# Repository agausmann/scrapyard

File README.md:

# scrapyard

Turning salvaged electronics into MIDI instruments

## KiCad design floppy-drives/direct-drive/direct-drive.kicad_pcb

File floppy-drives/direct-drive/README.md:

# Direct Drive

A floppy drive driver that attaches directly to the drive's IDC connector.

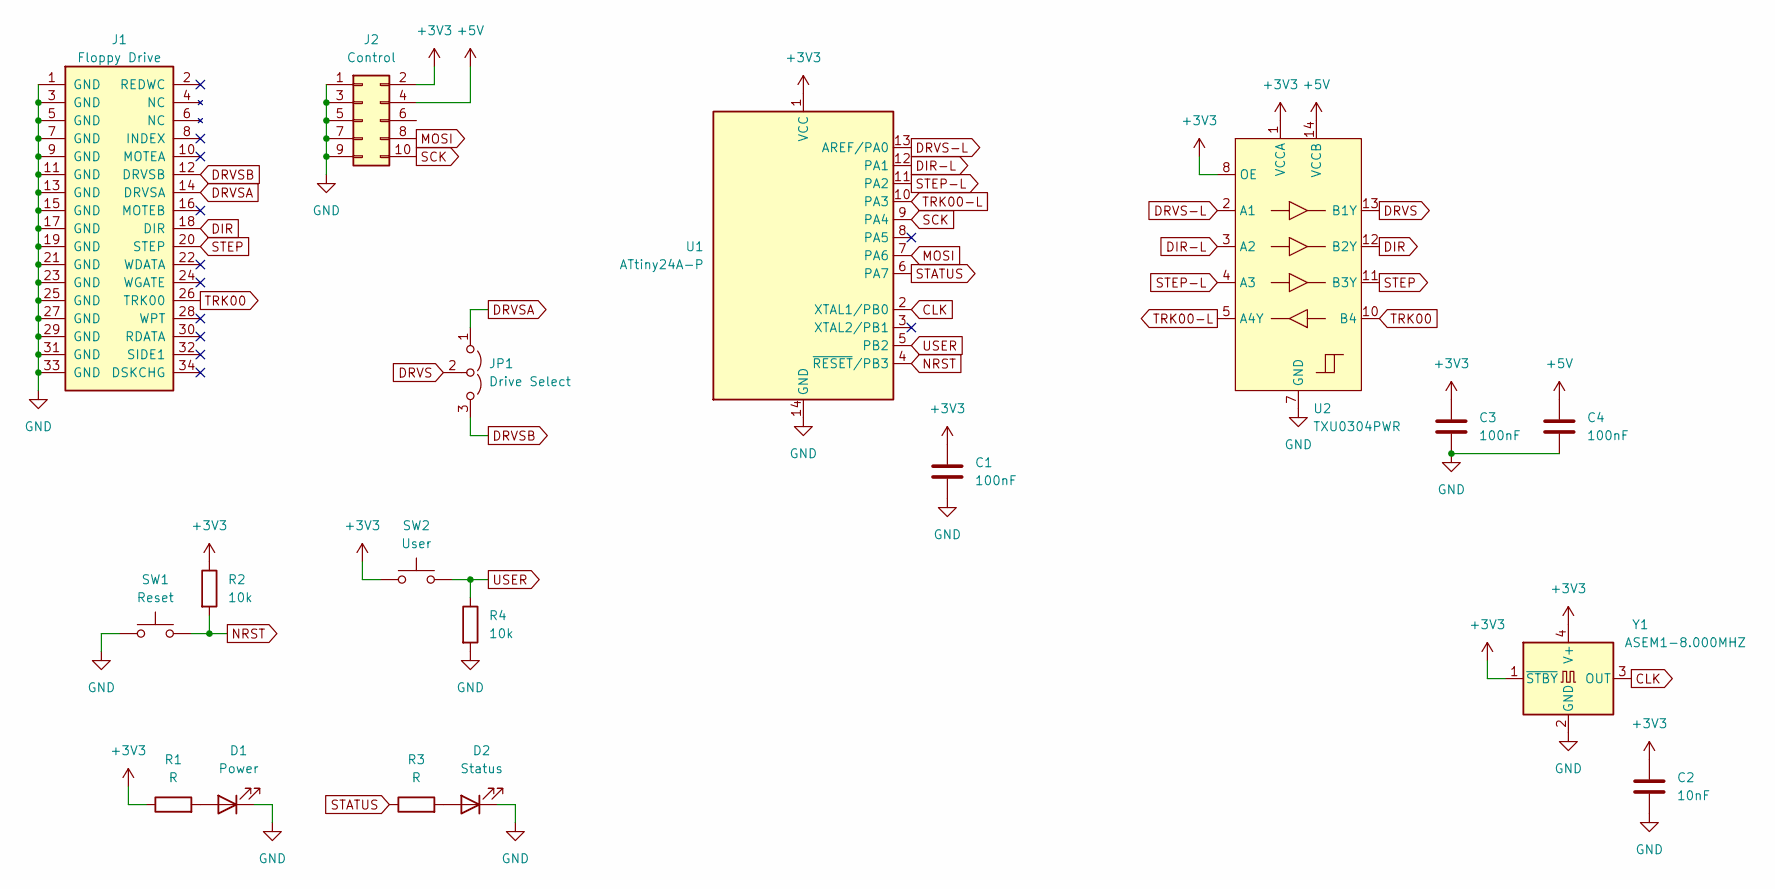
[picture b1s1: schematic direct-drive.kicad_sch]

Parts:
C1, C3, C4: 100nF; C_0603_1608Metric; Digikey 1276-1005-1-ND
C2: 10nF; C_0603_1608Metric; Digikey 1276-1926-1-ND
D1: Power; LED_0603_1608Metric; Digikey 732-4978-1-ND
D2: Status; LED_0603_1608Metric; Digikey 732-4971-1-ND
J1: Floppy Drive; IDC-Header_2x17_P2.54mm_Horizontal; Digikey S9207-ND
J2: Control; IDC-Header_2x05_P2.54mm_Horizontal; Digikey ED10533-ND
JP1: Drive Select; PinHeader_1x03_P2.54mm_Vertical
R1, R3: R; R_0603_1608Metric
R2, R4: 10k; R_0603_1608Metric
SW1: Reset; SW_Push_1P1T_NO_6x6mm_H9.5mm; Digikey CKN10880CT-ND
SW2: User; SW_Push_1P1T_NO_6x6mm_H9.5mm; Digikey CKN10880CT-ND
U1: ATtiny24A-P; DIP-14_W7.62mm; Digikey ED3045-5-ND
U2: TXU0304PWR; TSSOP-14_4.4x5mm_P0.65mm; Digikey 296-TXU0304PWRCT-ND
Y1: ASEM1-8.000MHZ; ASEM-4Pin-3.2x2.5mm; Digikey 535-9754-1-ND

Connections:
+3V3: C1.1, C2.1, C3.1, J2.2, R1.1, R2.1, SW2.1, U1.1 (VCC), U2.1 (VCCA), U2.8 (OE), Y1.1 (~STBY), Y1.4 (V+)
+5V: C4.1, J2.4, U2.14 (VCCB)
CLK: U1.2 (XTAL1/PB0), Y1.3 (OUT)
DIR: J1.18 (DIR), U2.12 (B2Y)
DIR-L: U1.12 (PA1), U2.3 (A2)
DRVS: JP1.2 (C), U2.13 (B1Y)
DRVS-L: U1.13 (AREF/PA0), U2.2 (A1)
DRVSA: J1.14 (DRVSA), JP1.1 (A)
DRVSB: J1.12 (DRVSB), JP1.3 (B)
GND: C1.2, C2.2, C3.2, C4.2, D1.1 (K), D2.1 (K), J1.1 (GND), J1.3 (GND), J1.5 (GND), J1.7 (GND), J1.9 (GND), J1.11 (GND), J1.13 (GND), J1.15 (GND), J1.17 (GND), J1.19 (GND), J1.21 (GND), J1.23 (GND), J1.25 (GND), J1.27 (GND), J1.29 (GND), J1.31 (GND), J1.33 (GND), J2.1, J2.3, J2.5, J2.7, J2.9, R4.2, SW1.1, U1.14 (GND), U2.7 (GND), Y1.2 (GND)
MOSI: J2.8, U1.7 (PA6)
NRST: R2.2, SW1.2, U1.4 (~RESET/PB3)
unnamed: D1.2 (A), R1.2
unnamed: D2.2 (A), R3.2
SCK: J2.10, U1.9 (PA4)
STATUS: R3.1, U1.6 (PA7)
STEP: J1.20 (STEP), U2.11 (B3Y)
STEP-L: U1.11 (PA2), U2.4 (A3)
TRK00: J1.26 (TRK00), U2.10 (B4)
TRK00-L: U1.10 (PA3), U2.5 (A4Y)
USER: R4.1, SW2.2, U1.5 (PB2)

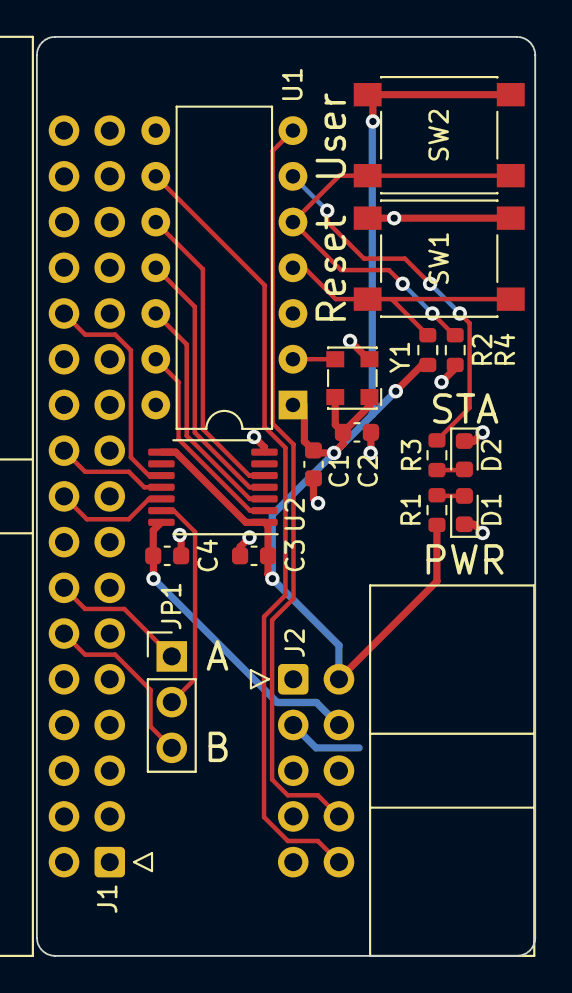
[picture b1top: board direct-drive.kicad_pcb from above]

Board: 2 copper layers, 27.7 x 51.1 mm, 18 parts (0 on the bottom side), 21 nets.

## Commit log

2022-02-11 Add README
2022-02-11 Add project for direct-drive PCBs
2022-02-11 direct-drive: Add LICENSE
2022-02-11 Create direct-drive schematic
2022-02-11 direct-drive: Add README
2022-02-13 Replace 7050 oscillator with 3225 and draft a PCB
2022-02-13 direct-drive schematic: Fix XO cap value and place caps near their corresponding chips.
2022-02-14 Add Digikey part numbers and missing 3D models
2022-02-14 direct-drive: Update schematic to use custom Conn_FloppyDrive symbol
2022-02-14 direct-drive: Move oscillator a little closer to the chip
